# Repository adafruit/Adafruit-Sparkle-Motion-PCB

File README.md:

## Adafruit Sparkle Motion - All-In-One WLED and xLights Board

<a href="http://www.adafruit.com/products/6100"><br/>
Click here to purchase one from the Adafruit shop</a>

PCB files for the Adafruit Sparkle Motion - All-In-One WLED and xLights Board

Format is EagleCAD schematic and board layout
* https://www.adafruit.com/product/6100

### Description

* Power via USB Type C PD with a slide switch that selects between 5, 12, and 20V (24V pixels can usually run fine at 20V) OR via a 2.1mm DC jack. With ideal diodes, it’s good for up to 5A from either.
* ESP32-Mini module with built-in or optional wFL antenna port. The classic ’32 has broad support, even if we’d prefer the ‘S2 or ‘S3.
* There are three output signal terminal block sets, with power and ground for each. They’ll be level-shifted to 5V.
* Built in I2S microphone (we’re still pondering this one).
* Stemma QT I2C port to connect external sensors/OLEDs/etc.; separate analog/digital input JST port.
* 1.3″x1.75″ / 33mm x 45mm size with mounting holes.

### License

Adafruit invests time and resources providing this open source design, please support Adafruit and open-source hardware by purchasing products from [Adafruit](https://www.adafruit.com)!

Designed by Limor Fried/Ladyada for Adafruit Industries.

Creative Commons Attribution/Share-Alike, all text above must be included in any redistribution. 
See license.txt for additional details.

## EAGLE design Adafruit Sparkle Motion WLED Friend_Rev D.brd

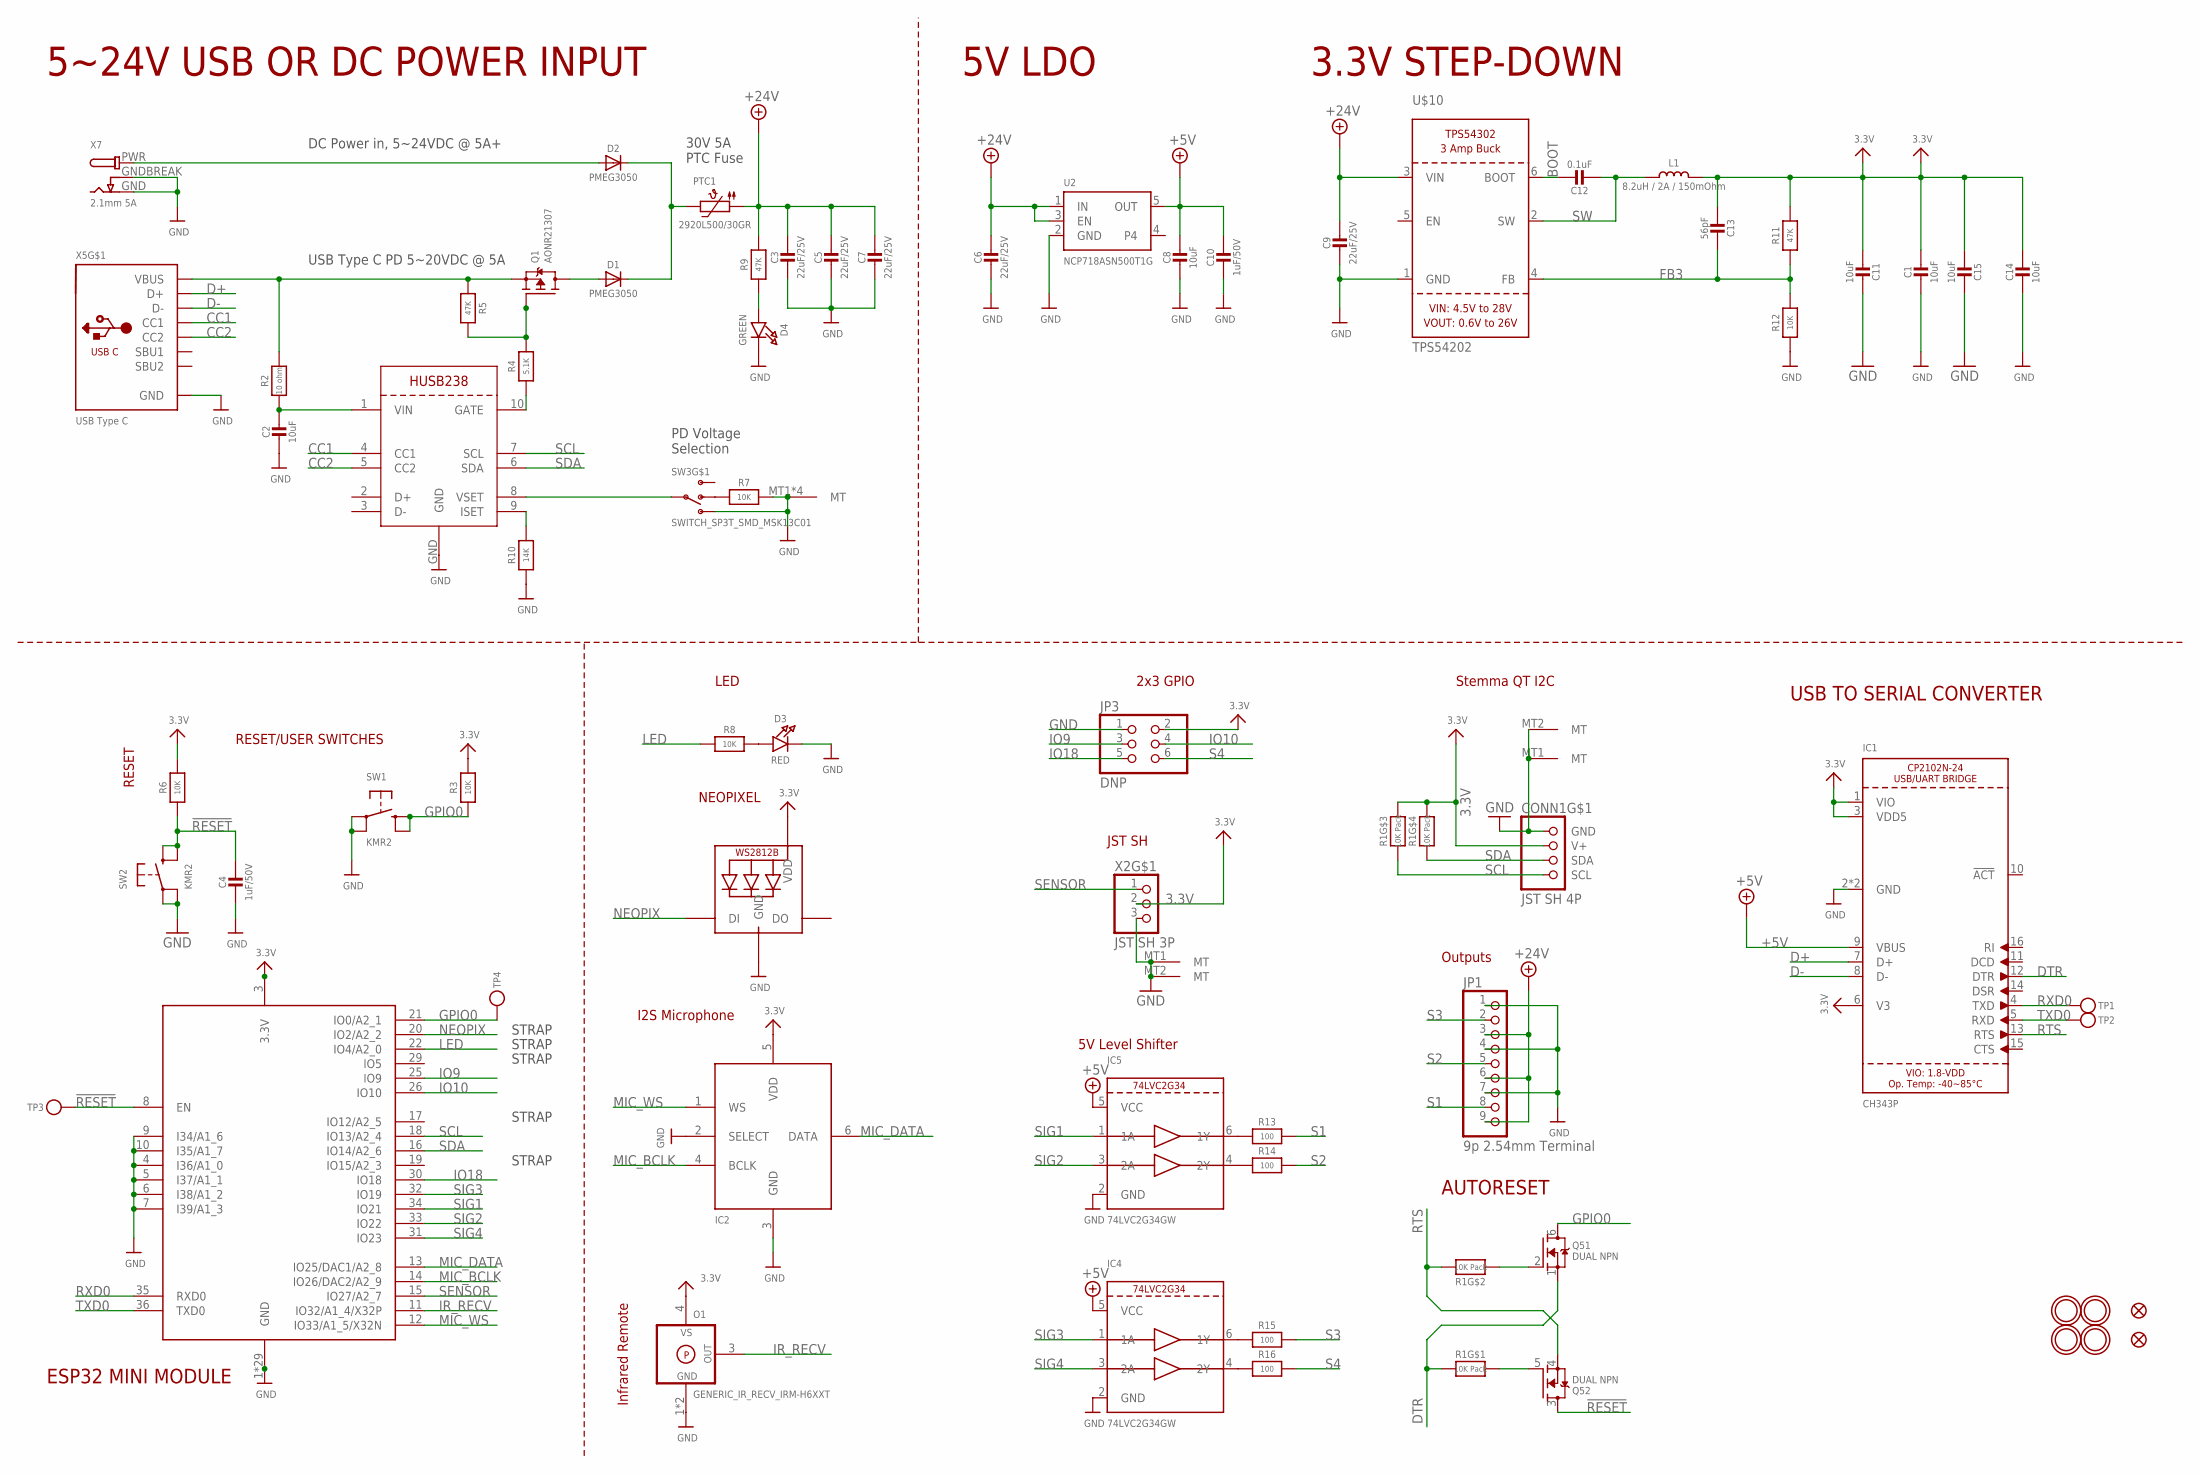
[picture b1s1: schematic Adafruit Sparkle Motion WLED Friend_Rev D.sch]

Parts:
C1, C2, C8, C11, C14, C15: 10uF; 0805-NO
C3, C5, C6, C7, C9: 22uF/25V; 0805-NO
C4, C10: 1uF/50V; 0603-NO
C12: 0.1uF; 0603-NO
C13: 56pF; 0603-NO
CONN1: JST SH 4P; JST_SH4
D1, D2: PMEG3050; SOD-128
D3: RED; CHIPLED_0603_NOOUTLINE
D4: GREEN; CHIPLED_0603_NOOUTLINE
IC1: CH343P; QFN16_3MM
IC2: ICS-43434; SPH0645LM4H
IC4, IC5: 74LVC2G34GW; SC70-6L
JP1: 9p 2.54mm Terminal; 1X09_2.54MMTERMINAL
JP3: DNP; 2X03_ROUND_70MIL
L1: 8.2uH / 2A / 150mOhm; INDUCTOR_5X5MM_NR5040_NOTHERMALS
LED1: WS2812B_SK6805_1515; SK6805_1515
O1: GENERIC_IR_RECV_IRM-H6XXT; IRM-H6XXT
PTC1: 2920L500/30GR; PTC2920
Q1: AONR21307; POWERDI3333
Q5: DUAL NPN; SOT363; JLC_ROTATION 0
R1: 10K Pack; RESPACK_4X0603
R2: 10 ohm; 0603-NO
R3, R6, R7, R8, R12: 10K; 0603-NO
R4: 5.1K; 0603-NO
R5, R9, R11: 47K; 0603-NO
R10: 14K; 0603-NO
R13, R14, R15, R16: 100; 0603-NO
SW1, SW2: KMR2; BTN_RKB2_4.6X2.8
SW3: SWITCH_SP3T_SMD_MSK13C01; MSK-13C01
TP1, TP2, TP3, TP4: TESTPOINTROUND1.5MM; TESTPOINT_ROUND_1.5MM
U2: NCP718ASN500T1G; SOT23-5; JLC_ROTATION 0
U$10: TPS54202; SOT23-6
U$14, U$20, U$28, U$31: MOUNTINGHOLE2.5; MOUNTINGHOLE_2.5_PLATED
U$34, U$35: FIDUCIAL_1MM
X2: JST SH 3P; JST_SH3
X3: HUSB238; DFN10_3X3MM
X4: ESP32-MINI-1
X5: USB Type C; USB_C_CUSB31-CFM2AX-01-X
X7: 2.1mm 5A; DCJACK_2MM_PTH

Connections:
3.3V: C1.1, C11.1, C13.2, C14.1, C15.1, CONN1.2 (V+), IC1.1 (VIO), IC1.3 (VDD5), IC1.6 (V3), IC2.5 (VDD), JP3.2, L1.P$2 (2), LED1.2 (VDD), O1.4 (VS), R1.5 (2), R1.6 (2), R3.2, R6.2, R11.2, X2.2, X4.3 (3.3V)
!RESET: C4.1, Q5.3 (D), R6.1, SW2.B (S), SW2.B' (S1), TP3.P$1, X4.8 (EN)
+5V: C8.1, C10.1, IC1.9 (VBUS), IC4.5 (VCC), IC5.5 (VCC), U2.5 (OUT)
+24V: C3.1, C5.1, C6.1, C7.1, C9.1, JP1.3, JP1.6, JP1.9, PTC1.P$1 (1), R9.2, U2.1 (IN), U2.3 (EN), U$10.3 (VIN)
BOOT: C12.1, U$10.6 (BOOT)
CC1: X3.4 (CC1), X5.A5 (CC1)
CC2: X3.5 (CC2), X5.B5 (CC2)
D+: IC1.7 (D+), X5.A6 (D+), X5.B6 (D+)
D-: IC1.8 (D-), X5.A7 (D-), X5.B7 (D-)
DTR: IC1.12 (DTR), Q5.1 (S), R1.1
FB3: C13.1, R11.1, R12.2, U$10.4 (FB)
GND: C1.2, C2.2, C3.2, C4.2, C5.2, C6.2, C7.2, C8.2, C9.2, C10.2, C11.2, C14.2, C15.2, CONN1.1 (GND), CONN1.MT1 (MT), CONN1.MT2 (MT), D3.C, D4.C, IC1.2 (GND), IC1.THERMAL (GND), IC2.2 (SELECT), IC2.3 (GND), IC4.2 (GND), IC5.2 (GND), JP1.1, JP1.4, JP1.7, JP3.1, LED1.4 (GND), O1.1 (GND), O1.2 (GND), R7.1, R10.1, R12.1, SW1.A, SW1.A' (P1), SW2.A, SW2.A' (P1), SW3.4 (3), SW3.MT1 (MT), SW3.MT2 (MT), SW3.MT3 (MT), SW3.MT4 (MT), U2.2 (GND), U$10.1 (GND), X2.3, X2.MT1 (MT), X2.MT2 (MT), X3.GND, X4.1 (GND), X4.2 (GND), X4.4 (I36/A1_0), X4.5 (I37/A1_1), X4.6 (I38/A1_2), X4.7 (I39/A1_3), X4.9 (I34/A1_6), X4.10 (I35/A1_7), X4.27 (GND), X4.38 (GND), X4.39 (GND), X4.40 (GND), X4.41 (GND), X4.42 (GND), X4.43 (GND), X4.44 (GND), X4.45 (GND), X4.46 (GND), X4.47 (GND), X4.48 (GND), X4.49 (GND), X4.50 (GND), X4.51 (GND), X4.52 (GND), X4.53 (GND), X4.54 (GND), X4.55 (GND), X4.56 (GND), X4.57 (GND), X4.58 (GND), X4.59 (GND), X4.60 (GND), X4.61 (GND), X4.62 (GND), X4.63 (GND), X5.A1B12 (GND), X5.B1A12 (GND), X7.GND, X7.GNDBREAK
GPIO0: Q5.6 (D), R3.1, SW1.B (S), SW1.B' (S1), TP4.P$1, X4.21 (IO0/A2_1)
IO9: JP3.3, X4.25 (IO9)
IO10: JP3.4, X4.26 (IO10)
IO18: JP3.5, X4.30 (IO18)
IR_RECV: O1.3 (OUT), X4.11 (IO32/A1_4/X32P)
LED: R8.1, X4.22 (IO4/A2_0)
MIC_BCLK: IC2.4 (BCLK), X4.14 (IO26/DAC2/A2_9)
MIC_DATA: IC2.6 (DATA), X4.13 (IO25/DAC1/A2_8)
MIC_WS: IC2.1 (WS), X4.12 (IO33/A1_5/X32N)
unnamed: D3.A, R8.2
unnamed: C2.1, R2.1, X3.1 (VIN)
unnamed: Q1.4 (G), R4.2, R5.2
unnamed: R4.1, X3.10 (GATE)
unnamed: SW3.3, X3.8 (VSET)
unnamed: R7.2, SW3.2
unnamed: Q5.5 (G), R1.8 (2)
unnamed: Q5.2 (G), R1.2 (1)
unnamed: D2.A, X7.PWR
unnamed: IC5.6 (1Y), R13.1
unnamed: IC5.4 (2Y), R14.1
unnamed: R10.2, X3.9 (ISET)
unnamed: D1.C, D2.C, PTC1.P$2 (2)
unnamed: D1.A, Q1.5678 (D)
unnamed: D4.A, R9.1
unnamed: IC4.6 (1Y), R15.1
unnamed: IC4.4 (2Y), R16.1
NEOPIX: LED1.1 (DI), X4.20 (IO2/A2_2)
RTS: IC1.13 (RTS), Q5.4 (S), R1.7 (2)
RXD0: IC1.4 (TXD), TP1.P$1, X4.35 (RXD0)
S1: JP1.8, R13.2
S2: JP1.5, R14.2
S3: JP1.2, R15.2
S4: JP3.6, R16.2
SCL: CONN1.4 (SCL), R1.3 (1), X3.7 (SCL), X4.18 (IO13/A2_4)
SDA: CONN1.3 (SDA), R1.4 (1), X3.6 (SDA), X4.16 (IO14/A2_6)
SENSOR: X2.1, X4.15 (IO27/A2_7)
SIG1: IC5.1 (1A), X4.34 (IO21)
SIG2: IC5.3 (2A), X4.33 (IO22)
SIG3: IC4.1 (1A), X4.32 (IO19)
SIG4: IC4.3 (2A), X4.31 (IO23)
SW: C12.2, L1.P$1 (1), U$10.2 (SW)
TXD0: IC1.5 (RXD), TP2.P$1, X4.36 (TXD0)
VBUS1: Q1.1 (S), Q1.2 (S), Q1.3 (S), R2.2, R5.1, X5.A4B9 (VBUS), X5.B4A9 (VBUS)

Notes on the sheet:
5~24V USB OR DC POWER INPUT
RESET
LED
NEOPIXEL
ESP32 MINI MODULE
RESET/USER SWITCHES
AUTORESET
USB TO SERIAL CONVERTER
DC Power in, 5~24VDC @ 5A+
USB Type C PD 5~20VDC @ 5A
30V 5A PTC Fuse
PD Voltage Selection
5V LDO
3.3V STEP-DOWN
STRAP
I2S Microphone
Infrared Remote
2x3 GPIO
JST SH
5V Level Shifter
Stemma QT I2C
Outputs

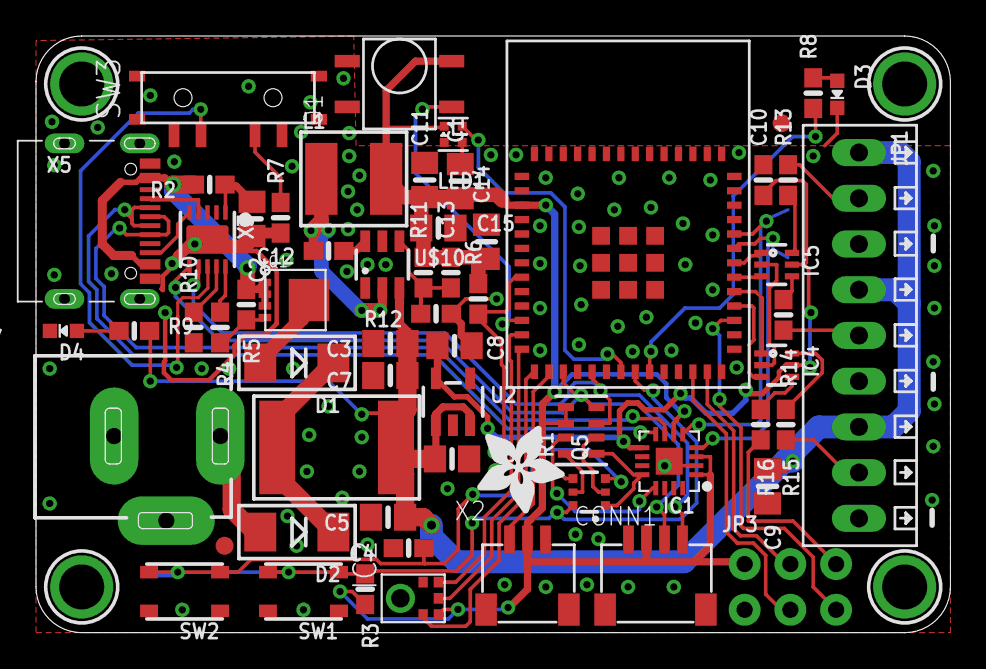
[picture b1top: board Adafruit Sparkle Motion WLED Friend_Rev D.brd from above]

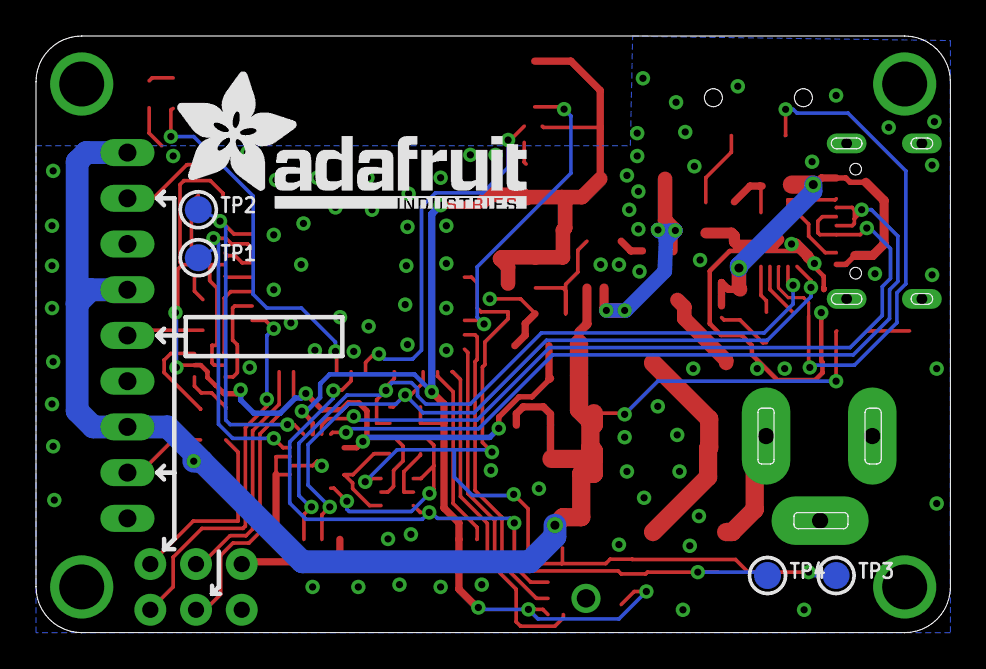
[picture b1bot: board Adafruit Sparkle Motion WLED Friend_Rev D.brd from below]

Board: 2 copper layers, 50.8 x 33.1 mm, 123 parts (36 on the bottom side), 55 nets.

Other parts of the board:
PLABEL0: PLABEL0
PLABEL1: PLABEL1
PLABEL2: PLABEL2
PLABEL3: PLABEL3
PLABEL4: PLABEL4
PLABEL6: PLABEL6
PLABEL7: PLABEL7
PLABEL8: PLABEL8
PLABEL9: PLABEL9
PLABEL10: PLABEL10
PLABEL11: PLABEL11
PLABEL13: PLABEL13
PLABEL14: PLABEL14
PLABEL16: PLABEL16
PLABEL17: PLABEL17
PLABEL19: PLABEL19
PLABEL20: PLABEL20
PLABEL21: PLABEL21
PLABEL22: PLABEL22
PLABEL23: PLABEL23
PLABEL24: PLABEL24
PLABEL25: PLABEL25
PLABEL26: PLABEL26
PLABEL27: PLABEL27
PLABEL28: PLABEL28
PLABEL29: PLABEL29
PLABEL30: PLABEL30
PLABEL31: PLABEL31
PLABEL32: PLABEL32
PLABEL33: PLABEL33
PLABEL34: PLABEL34
PLABEL35: PLABEL35
PLABEL36: PLABEL36
PLABEL37: PLABEL37
PLABEL38: PLABEL38
PLABEL39: PLABEL39
PLABEL40: PLABEL40
PLABEL41: PLABEL41
PLABEL42: PLABEL42
PLABEL43: PLABEL43
PLABEL44: PLABEL44
PLABEL45: PLABEL45
PLABEL46: PLABEL46
PLABEL47: PLABEL47
PLABEL48: PLABEL48
PLABEL49: PLABEL49
PLABEL50: PLABEL50
PLABEL51: PLABEL51
PLABEL52: PLABEL52
PLABEL53: PLABEL53
PLABEL54: PLABEL54
PLABEL55: PLABEL55
PLABEL56: PLABEL56
U$46: ADAFRUIT_5MM
U$50: ADAFRUIT_TEXT_20MM

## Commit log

2024-12-18 cookiecutter
2025-01-15 shop image & final board silk
2025-01-27 adding prettypins
2025-01-27 rename prettypins
2025-09-25 rev d

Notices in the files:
parts and their libraries:
microbuilder: This work is placed in the public domain, and may be freely used for commercial and non-commercial work with the following conditions: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
